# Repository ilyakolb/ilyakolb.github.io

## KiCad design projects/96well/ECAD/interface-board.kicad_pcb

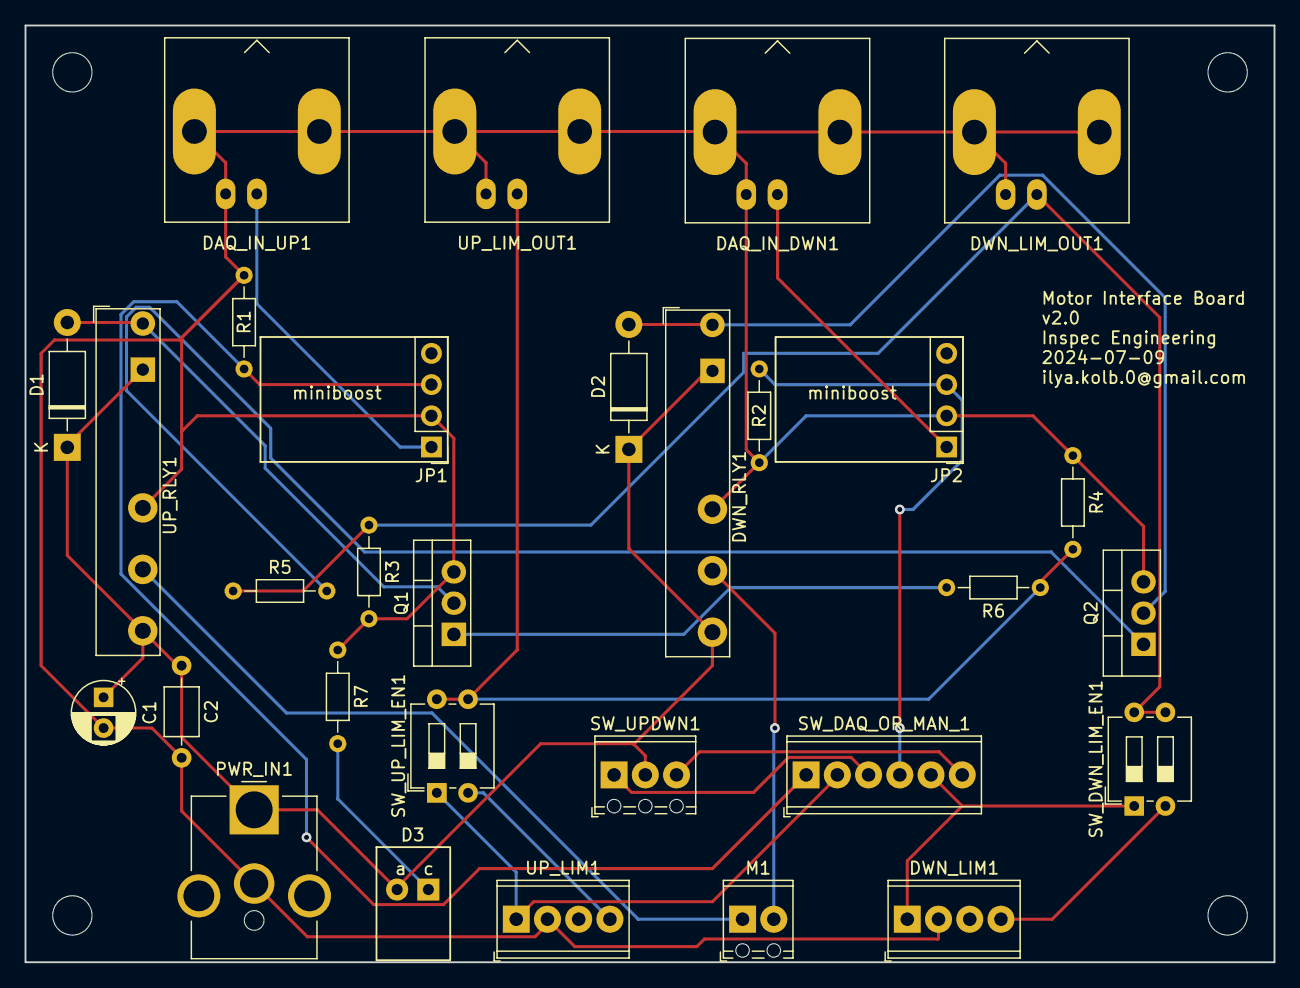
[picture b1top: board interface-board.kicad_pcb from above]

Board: 2 copper layers, 101.6 x 76.2 mm, 30 parts (0 on the bottom side), 21 nets.

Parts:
C1: 10uF; CP_Radial_D5.0mm_P2.50mm
C2: 0.1uF; C_Axial_L3.8mm_D2.6mm_P7.50mm_Horizontal
D1, D2: 1N4001; D_DO-41_SOD81_P10.16mm_Horizontal
D3: LED; LED_W6mm_L9.2mm_Pitch2.54mm
DAQ_IN_DWN1: Conn_Coaxial; BNC_Amphenol_B6252HB-NPP3G-50_Horizontal
DAQ_IN_UP1: Conn_Coaxial; BNC_Amphenol_B6252HB-NPP3G-50_Horizontal
DWN_LIM1: PM-25; TerminalBlock_Phoenix_MPT-0,5-4-2.54_1x04_P2.54mm_Horizontal
DWN_LIM_OUT1: Conn_Coaxial; BNC_Amphenol_B6252HB-NPP3G-50_Horizontal
DWN_RLY1: FINDER-34.51; Relay_SPDT_Finder_34.51_Vertical
JP1, JP2: HEADER-1X4ROUND; PinHeader_1x04_P2.54mm_Vertical
M1: Motor_DC_ALT; TerminalBlock_Phoenix_MPT-0,5-2-2.54_1x02_P2.54mm_Horizontal
PWR_IN1: Barrel_Jack_MountingPin; BarrelJack_CUI_PJ-063AH_Horizontal_CircularHoles
Q1, Q2: IRLB8721PBF; TO-220-3_Vertical
R1, R2, R3, R4: 10k; R_Axial_DIN0204_L3.6mm_D1.6mm_P7.62mm_Horizontal
R5, R6, R7: 330; R_Axial_DIN0204_L3.6mm_D1.6mm_P7.62mm_Horizontal
SW_DAQ_OR_MAN_1: SW_DAQ_OR_MAN; TerminalBlock_Phoenix_MPT-0,5-6-2.54_1x06_P2.54mm_Horizontal
SW_DWN_LIM_EN1: SW_DIP_x02; SW_DIP_SPSTx02_Slide_6.7x6.64mm_W7.62mm_P2.54mm_LowProfile
SW_UPDWN1: SW_Push_SPDT; TerminalBlock_Phoenix_MPT-0,5-3-2.54_1x03_P2.54mm_Horizontal
SW_UP_LIM_EN1: SW_DIP_x02; SW_DIP_SPSTx02_Slide_6.7x6.64mm_W7.62mm_P2.54mm_LowProfile
UP_LIM1: PM-25; TerminalBlock_Phoenix_MPT-0,5-4-2.54_1x04_P2.54mm_Horizontal
UP_LIM_OUT1: Conn_Coaxial; BNC_Amphenol_B6252HB-NPP3G-50_Horizontal
UP_RLY1: FINDER-34.51; Relay_SPDT_Finder_34.51_Vertical

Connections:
GND: C1.2, C2.2, DAQ_IN_DWN1.2 (Ext), DAQ_IN_UP1.2 (Ext), DWN_LIM1.2 (GND), DWN_LIM_OUT1.2 (Ext), DWN_RLY1.12, JP1.2 (GND), JP2.2 (GND), PWR_IN1.2, Q1.3 (S), Q2.3 (S), R1.1, R2.1, R3.2, R4.1, R7.1, UP_LIM1.2 (GND), UP_LIM_OUT1.2 (Ext), UP_RLY1.12
unnamed: D1.2 (A), Q1.2 (D), UP_RLY1.A2
unnamed: D2.2 (A), DWN_RLY1.A2, Q2.2 (D)
unnamed: D3.1 (K), R7.2
unnamed: DAQ_IN_DWN1.1 (In), JP2.1 (VIN)
unnamed: DAQ_IN_UP1.1 (In), JP1.1 (VIN)
unnamed: DWN_LIM1.1 (+V), SW_DAQ_OR_MAN_1.5 (B), SW_DWN_LIM_EN1.1
unnamed: DWN_LIM1.4 (OUT1), SW_DWN_LIM_EN1.2
unnamed: DWN_LIM_OUT1.1 (In), R3.1, R5.1, SW_DWN_LIM_EN1.3, SW_DWN_LIM_EN1.4
unnamed: JP1.3 (VO), R1.2, SW_DAQ_OR_MAN_1.1 (A)
unnamed: JP2.3 (VO), R2.2, SW_DAQ_OR_MAN_1.4 (A)
unnamed: M1.1 (+), UP_RLY1.11
unnamed: DWN_RLY1.11, M1.2 (-)
unnamed: Q1.1 (G), R6.2
unnamed: Q2.1 (G), R5.2
unnamed: SW_DAQ_OR_MAN_1.2 (B), SW_UP_LIM_EN1.1, UP_LIM1.1 (+V)
unnamed: SW_DAQ_OR_MAN_1.3 (C), SW_UPDWN1.1 (A)
unnamed: SW_DAQ_OR_MAN_1.6 (C), SW_UPDWN1.3 (C)
unnamed: SW_UP_LIM_EN1.2, UP_LIM1.4 (OUT1)
unnamed: R4.2, R6.1, SW_UP_LIM_EN1.3, SW_UP_LIM_EN1.4, UP_LIM_OUT1.1 (In)
VCC: C1.1, C2.1, D1.1 (K), D2.1 (K), D3.2 (A), DWN_RLY1.14, DWN_RLY1.A1, PWR_IN1.1, SW_UPDWN1.2 (B), UP_RLY1.14, UP_RLY1.A1

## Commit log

2024-06-27 starting revamp
    - update Gemfile to launch server locally
    - update about, basic details
2024-06-29 projects wip
2024-07-01 add 96stim project
2024-07-17 add 96well project content
2024-07-17 add new publication pages
2024-07-18 update images
2024-07-21 more details in 96well, project images
2024-07-22 remove wellstim; minor wording
2024-07-22 update google scholar
2024-07-22 title change
2024-07-22 fix formatting, typos
